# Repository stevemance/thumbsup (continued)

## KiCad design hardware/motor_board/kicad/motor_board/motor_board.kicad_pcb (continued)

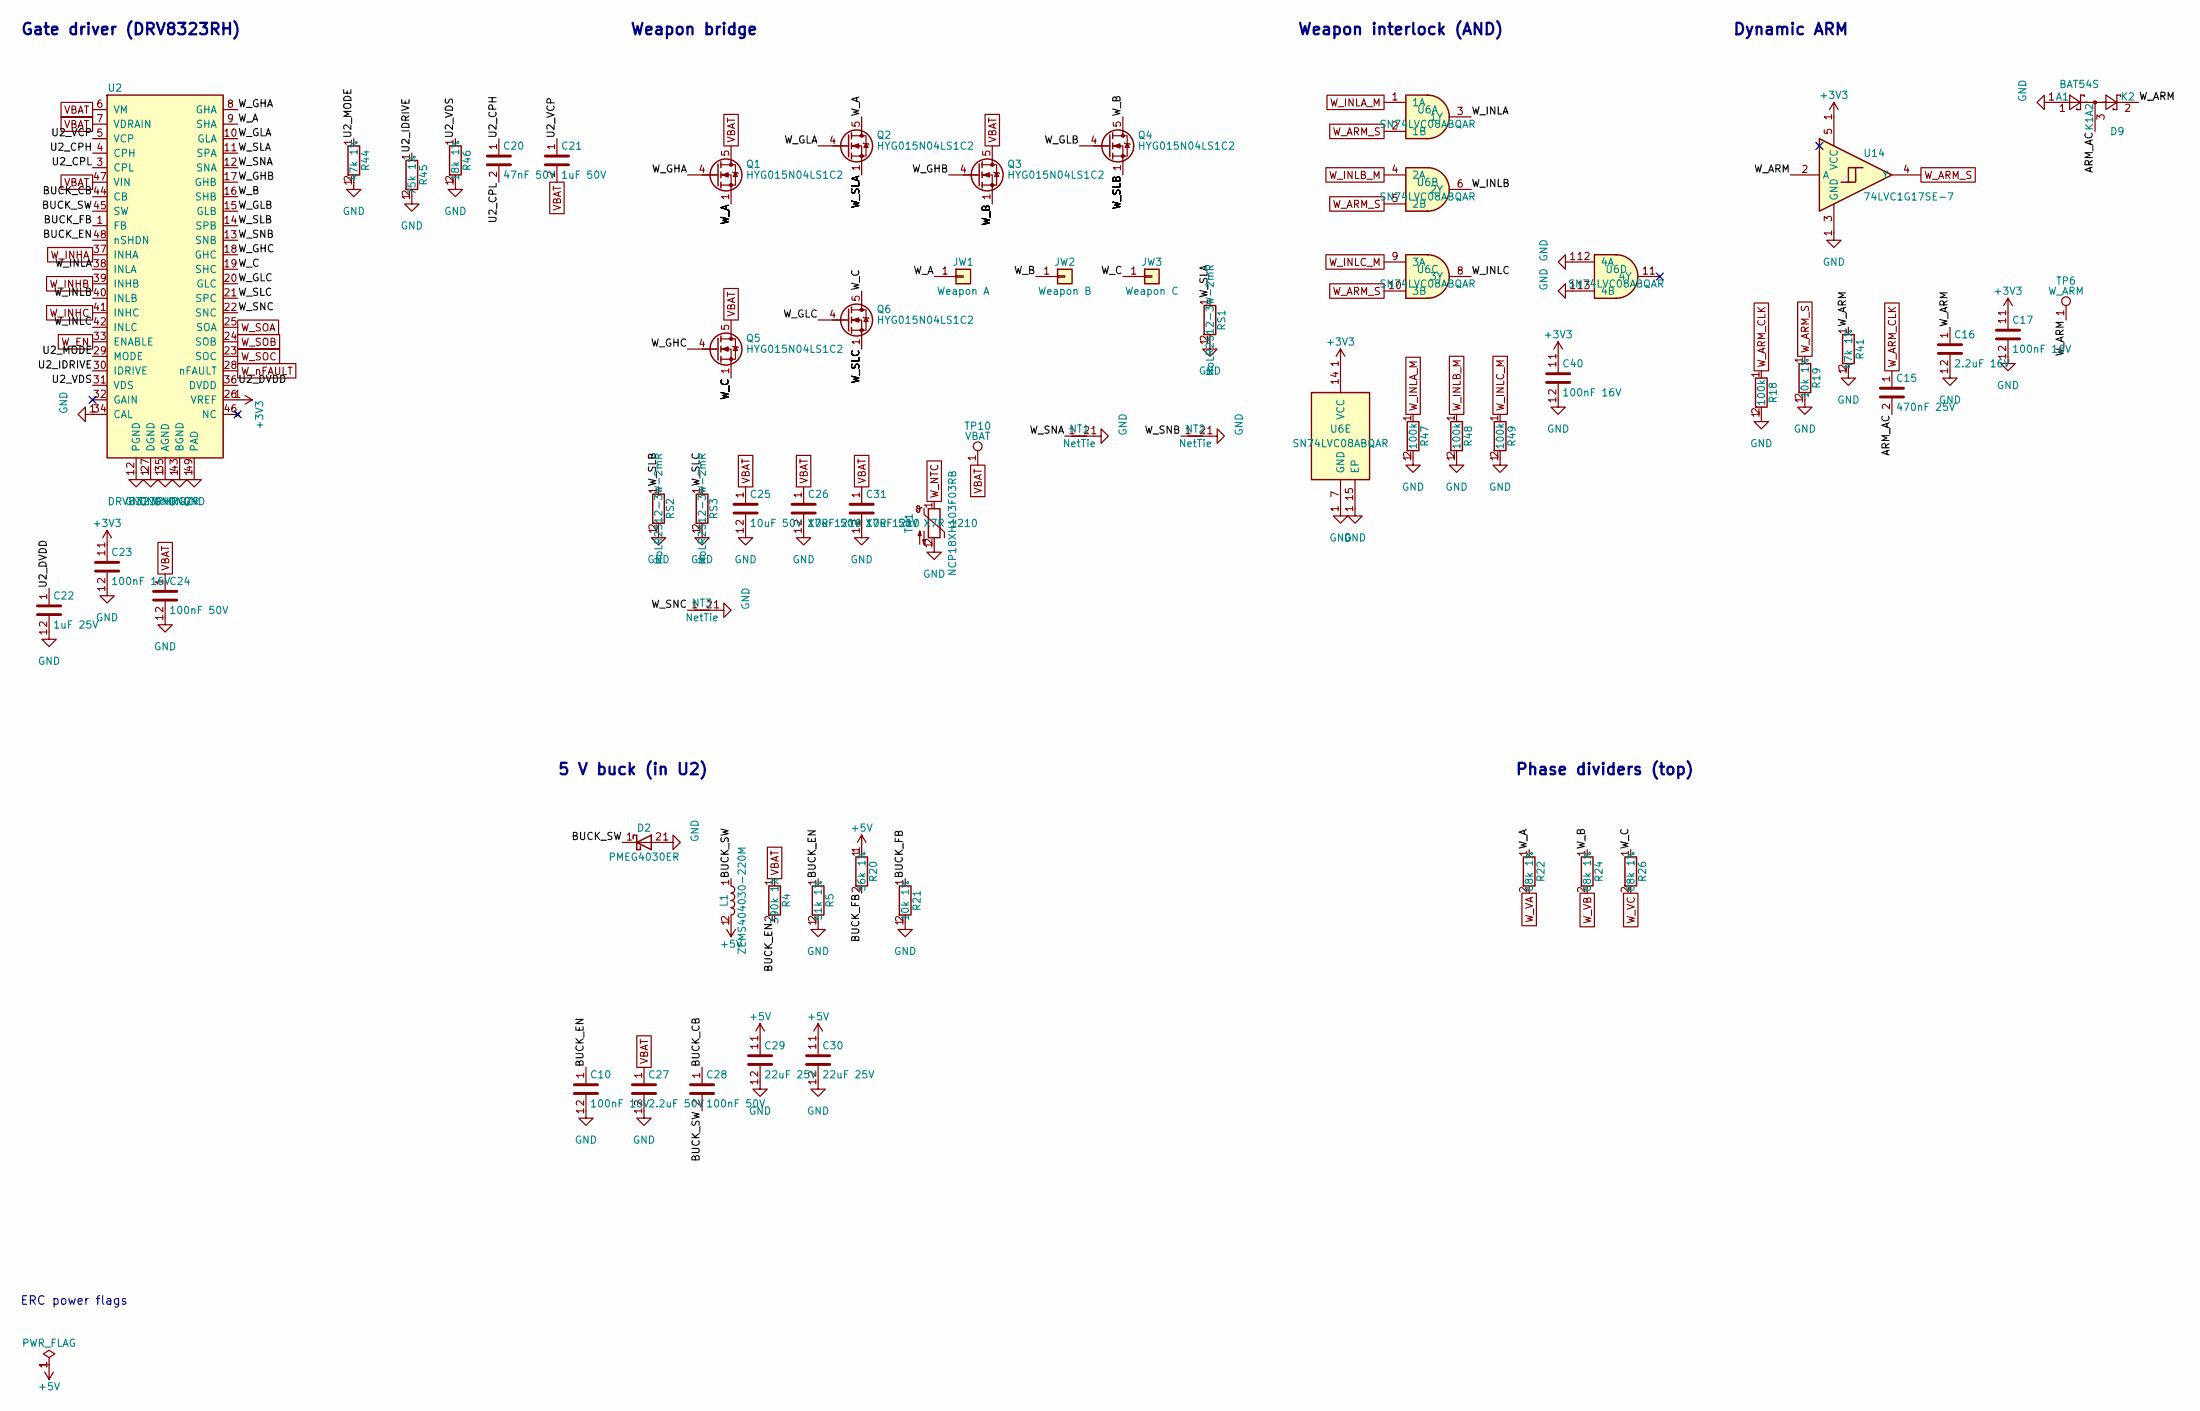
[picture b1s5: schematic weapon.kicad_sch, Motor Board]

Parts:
C10, C17, C23, C40: 100nF 16V; C_0402_1005Metric; LCSC C1525
C15: 470nF 25V; C_0603_1608Metric; LCSC C1623
C16: 2.2uF 16V; C_0603_1608Metric; LCSC C23630
C20: 47nF 50V; C_0603_1608Metric; LCSC C1622
C21: 1uF 50V; C_0603_1608Metric; LCSC C15849
C22: 1uF 25V; C_0402_1005Metric; LCSC C52923
C24, C28: 100nF 50V; C_0603_1608Metric; LCSC C14663
C25, C26, C31: 10uF 50V X7R 1210; C_1210_3225Metric; LCSC C77102
C27: 2.2uF 50V; C_0805_2012Metric; LCSC C377773
C29, C30: 22uF 25V; C_0805_2012Metric; LCSC C45783
D2: PMEG4030ER; Nexperia_CFP3_SOD-123W; MPN PMEG4030ER; LCSC C389355
D9: BAT54S; SOT-23; MPN BAT54S; LCSC C47546
JW1: Weapon A; SolderWire-1.5sqmm_1x01_D1.7mm_OD3.9mm
JW2: Weapon B; SolderWire-1.5sqmm_1x01_D1.7mm_OD3.9mm
JW3: Weapon C; SolderWire-1.5sqmm_1x01_D1.7mm_OD3.9mm
L1: ZEMS404030-220M; L_Changjiang_FTC404030S; MPN ZEMS404030-220M; LCSC C49009291
NT1, NT2, NT3: NetTie; NetTie-2_SMD_Pad0.5mm
Q1, Q2, Q3, Q4, Q5, Q6: HYG015N04LS1C2; PQFN-8-EP_6x5mm_P1.27mm_Generic; MPN HYG015N04LS1C2; LCSC C2874970
R4: 390k 1%; R_0603_1608Metric; LCSC C137735
R5: 51k 1%; R_0402_1005Metric; LCSC C25794
R18, R47, R48, R49: 100k; R_0402_1005Metric; LCSC C25741
R19, R21: 10k 1%; R_0402_1005Metric; LCSC C25744
R20: 56k 1%; R_0402_1005Metric; LCSC C25796
R22, R24, R26: 68k 1%; R_0402_1005Metric; LCSC C36871
R41, R44: 47k 1%; R_0402_1005Metric; LCSC C25792
R45: 75k 1%; R_0402_1005Metric; LCSC C25798
R46: 18k 1%; R_0402_1005Metric; LCSC C25762
RS1, RS2, RS3: HoLR2512-3W-2mR; R_2512_HoLR_1-4mR; MPN HoLR2512-3W-2mR; LCSC C2844506
TH1: NCP18XH103F03RB; R_0603_1608Metric; LCSC C13564
TP6: W_ARM; TestPoint_Pad_D1.0mm
TP10: VBAT; TestPoint_Pad_D1.0mm
U2: DRV8323RHRGZR; Texas_RGZ0048A_VQFN-48-1EP_7x7mm_P0.5mm_EP5.15x5.15mm; MPN DRV8323RHRGZR; LCSC C543035
U6: SN74LVC08ABQAR; DHWQFN-14-1EP_2.5x3mm_P0.5mm_EP1x1.5mm; MPN SN74LVC08ABQAR; LCSC C31971766
U14: 74LVC1G17SE-7; SOT-353_SC-70-5; MPN 74LVC1G17SE-7; LCSC C212314

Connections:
+3V3: C17.1, C23.1, C40.1, U2.26 (VREF), U6.14 (VCC), U14.5 (VCC); also elsewhere on the board
+5V: C29.1, C30.1, L1.2, R20.1; also elsewhere on the board
/weapon/ARM_AC: C15.2, D9.3 (K1A2)
/weapon/BUCK_CB: C28.1, U2.44 (CB)
/weapon/BUCK_EN: C10.1, R4.2, R5.1, U2.48 (nSHDN)
/weapon/BUCK_FB: R20.2, R21.1, U2.1 (FB)
/weapon/BUCK_SW: C28.2, D2.1 (K), L1.1, U2.45 (SW)
/weapon/U2_CPH: C20.1, U2.4 (CPH)
/weapon/U2_CPL: C20.2, U2.3 (CPL)
/weapon/U2_DVDD: C22.1, U2.36 (DVDD)
/weapon/U2_IDRIVE: R45.1, U2.30 (IDRIVE)
/weapon/U2_MODE: R44.1, U2.29 (MODE)
/weapon/U2_VCP: C21.1, U2.5 (VCP)
/weapon/U2_VDS: R46.1, U2.31 (VDS)
/weapon/W_A: JW1.1, Q1.1 (S), Q1.2 (S), Q1.3 (S), Q2.5 (D), R22.1, U2.9 (SHA)
/weapon/W_ARM: C16.1, D9.2 (K2), R41.1, TP6.1, U14.2 (A)
/weapon/W_B: JW2.1, Q3.1 (S), Q3.2 (S), Q3.3 (S), Q4.5 (D), R24.1, U2.16 (SHB)
/weapon/W_C: JW3.1, Q5.1 (S), Q5.2 (S), Q5.3 (S), Q6.5 (D), R26.1, U2.19 (SHC)
/weapon/W_GHA: Q1.4 (G), U2.8 (GHA)
/weapon/W_GHB: Q3.4 (G), U2.17 (GHB)
/weapon/W_GHC: Q5.4 (G), U2.18 (GHC)
/weapon/W_GLA: Q2.4 (G), U2.10 (GLA)
/weapon/W_GLB: Q4.4 (G), U2.15 (GLB)
/weapon/W_GLC: Q6.4 (G), U2.20 (GLC)
/weapon/W_INLA: U2.38 (INLA), U6.3 (1Y)
/weapon/W_INLB: U2.40 (INLB), U6.6 (2Y)
/weapon/W_INLC: U2.42 (INLC), U6.8 (3Y)
/weapon/W_SLA: Q2.1 (S), Q2.2 (S), Q2.3 (S), RS1.1, U2.11 (SPA)
/weapon/W_SLB: Q4.1 (S), Q4.2 (S), Q4.3 (S), RS2.1, U2.14 (SPB)
/weapon/W_SLC: Q6.1 (S), Q6.2 (S), Q6.3 (S), RS3.1, U2.21 (SPC)
/weapon/W_SNA: NT1.1, U2.12 (SNA)
/weapon/W_SNB: NT2.1, U2.13 (SNB)
/weapon/W_SNC: NT3.1, U2.22 (SNC)
GND: C10.2, C16.2, C17.2, C22.2, C23.2, C24.2, C25.2, C26.2, C27.2, C29.2, C30.2, C31.2, C40.2, D2.2 (A), D9.1 (A1), NT1.2, NT2.2, NT3.2, R5.2, R18.2, R19.2, R21.2, R41.2, R44.2, R45.2, R46.2, R47.2, R48.2, R49.2, RS1.2, RS2.2, RS3.2, TH1.2, U2.2 (PGND), U2.27 (DGND), U2.34 (CAL), U2.35 (AGND), U2.43 (BGND), U2.49 (PAD), U6.7 (GND), U6.12 (4A), U6.13 (4B), U6.15 (EP), U14.3 (GND); also elsewhere on the board
VBAT: C21.2, C24.1, C25.1, C26.1, C27.1, C31.1, Q1.5 (D), Q3.5 (D), Q5.5 (D), R4.1, TP10.1, U2.6 (VM), U2.7 (VDRAIN), U2.47 (VIN); also elsewhere on the board
W_ARM_CLK: C15.1, R18.1; also elsewhere on the board
W_ARM_S: R19.1, U6.2 (1B), U6.5 (2B), U6.10 (3B), U14.4 (Y); also elsewhere on the board
W_EN: U2.33 (ENABLE); also elsewhere on the board
W_INHA: U2.37 (INHA); also elsewhere on the board
W_INHB: U2.39 (INHB); also elsewhere on the board
W_INHC: U2.41 (INHC); also elsewhere on the board
W_INLA_M: R47.1, U6.1 (1A); also elsewhere on the board
W_INLB_M: R48.1, U6.4 (2A); also elsewhere on the board
W_INLC_M: R49.1, U6.9 (3A); also elsewhere on the board
W_NTC: TH1.1; also elsewhere on the board
W_SOA: U2.25 (SOA); also elsewhere on the board
W_SOB: U2.24 (SOB); also elsewhere on the board
W_SOC: U2.23 (SOC); also elsewhere on the board
W_VA: R22.2; also elsewhere on the board
W_VB: R24.2; also elsewhere on the board
W_VC: R26.2; also elsewhere on the board
W_nFAULT: U2.28 (nFAULT); also elsewhere on the board

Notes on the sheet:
ERC power flags
Gate driver (DRV8323RH)
Weapon bridge
Weapon interlock (AND)
Dynamic ARM
5 V buck (in U2)
Phase dividers (top)

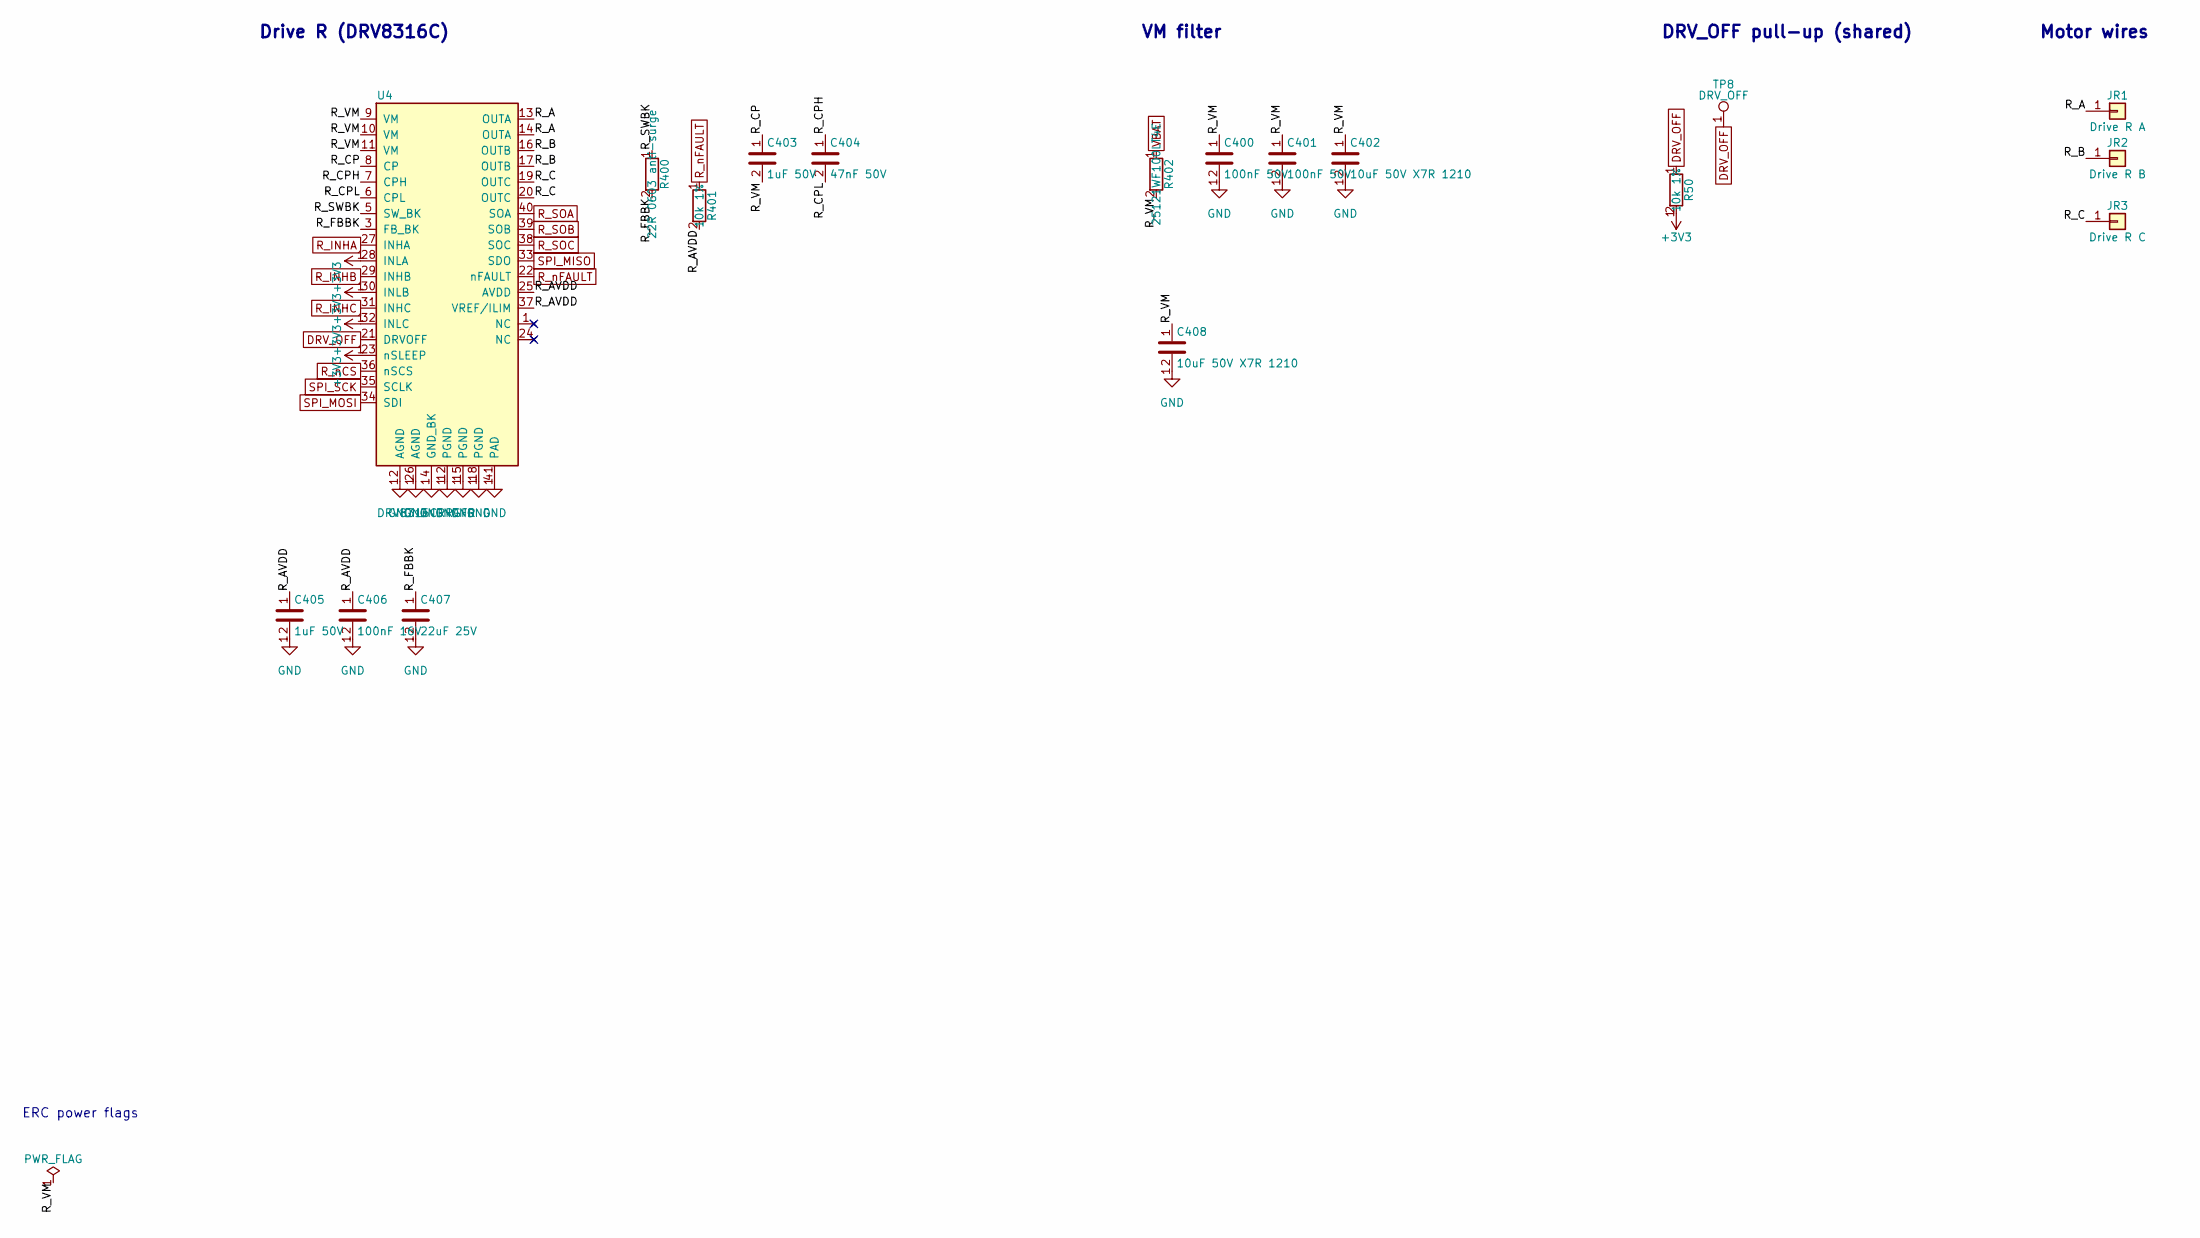
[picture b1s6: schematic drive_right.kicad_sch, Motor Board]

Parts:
C400, C401: 100nF 50V; C_0603_1608Metric; LCSC C14663
C402, C408: 10uF 50V X7R 1210; C_1210_3225Metric; LCSC C77102
C403, C405: 1uF 50V; C_0603_1608Metric; LCSC C15849
C404: 47nF 50V; C_0603_1608Metric; LCSC C1622
C406: 100nF 16V; C_0402_1005Metric; LCSC C1525
C407: 22uF 25V; C_0805_2012Metric; LCSC C45783
JR1: Drive R A; SolderWire-0.5sqmm_1x01_D0.9mm_OD2.1mm
JR2: Drive R B; SolderWire-0.5sqmm_1x01_D0.9mm_OD2.1mm
JR3: Drive R C; SolderWire-0.5sqmm_1x01_D0.9mm_OD2.1mm
R50, R401: 10k 1%; R_0402_1005Metric; LCSC C25744
R400: 22R 0603 anti-surge; R_0603_1608Metric; LCSC C2074038
R402: 25121WF100LT4E; R_2512_6332Metric; MPN 25121WF100LT4E; LCSC C25466
TP8: DRV_OFF; TestPoint_Pad_D1.0mm
U4: DRV8316CRRGFR; TI_RGF0040E_VQFN-40-1EP_5x7mm_P0.5mm_EP3.7x5.7mm; MPN DRV8316CRRGFR; LCSC C5447274

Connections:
+3V3: R50.2, U4.23 (nSLEEP), U4.28 (INLA), U4.30 (INLB), U4.32 (INLC); also elsewhere on the board
/drive_right/R_A: JR1.1, U4.13 (OUTA), U4.14 (OUTA)
/drive_right/R_AVDD: C405.1, C406.1, R401.2, U4.25 (AVDD), U4.37 (VREF/ILIM)
/drive_right/R_B: JR2.1, U4.16 (OUTB), U4.17 (OUTB)
/drive_right/R_C: JR3.1, U4.19 (OUTC), U4.20 (OUTC)
/drive_right/R_CP: C403.1, U4.8 (CP)
/drive_right/R_CPH: C404.1, U4.7 (CPH)
/drive_right/R_CPL: C404.2, U4.6 (CPL)
/drive_right/R_FBBK: C407.1, R400.2, U4.3 (FB_BK)
/drive_right/R_SWBK: R400.1, U4.5 (SW_BK)
/drive_right/R_VM: C400.1, C401.1, C402.1, C403.2, C408.1, R402.2, U4.9 (VM), U4.10 (VM), U4.11 (VM)
DRV_OFF: R50.1, TP8.1, U4.21 (DRVOFF); also elsewhere on the board
GND: C400.2, C401.2, C402.2, C405.2, C406.2, C407.2, C408.2, U4.2 (AGND), U4.4 (GND_BK), U4.12 (PGND), U4.15 (PGND), U4.18 (PGND), U4.26 (AGND), U4.41 (PAD); also elsewhere on the board
R_INHA: U4.27 (INHA); also elsewhere on the board
R_INHB: U4.29 (INHB); also elsewhere on the board
R_INHC: U4.31 (INHC); also elsewhere on the board
R_SOA: U4.40 (SOA); also elsewhere on the board
R_SOB: U4.39 (SOB); also elsewhere on the board
R_SOC: U4.38 (SOC); also elsewhere on the board
R_nCS: U4.36 (nSCS); also elsewhere on the board
R_nFAULT: R401.1, U4.22 (nFAULT); also elsewhere on the board
SPI_MISO: U4.33 (SDO); also elsewhere on the board
SPI_MOSI: U4.34 (SDI); also elsewhere on the board
SPI_SCK: U4.35 (SCLK); also elsewhere on the board
VBAT: R402.1; also elsewhere on the board

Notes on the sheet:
ERC power flags
Drive R (DRV8316C)
VM filter
DRV_OFF pull-up (shared)
Motor wires

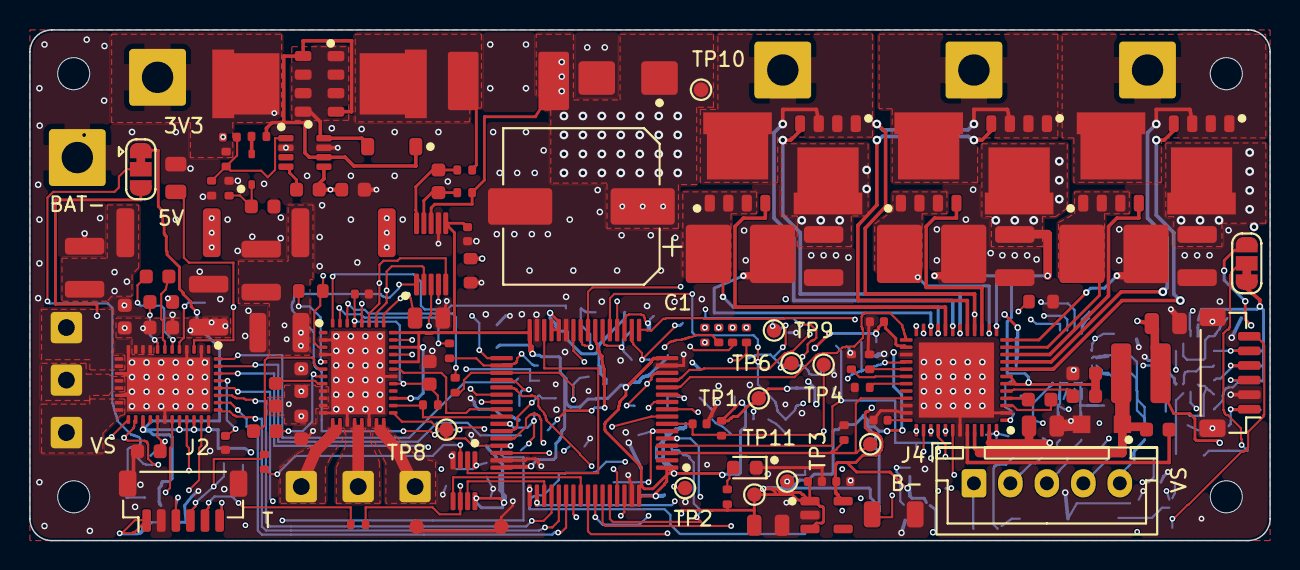
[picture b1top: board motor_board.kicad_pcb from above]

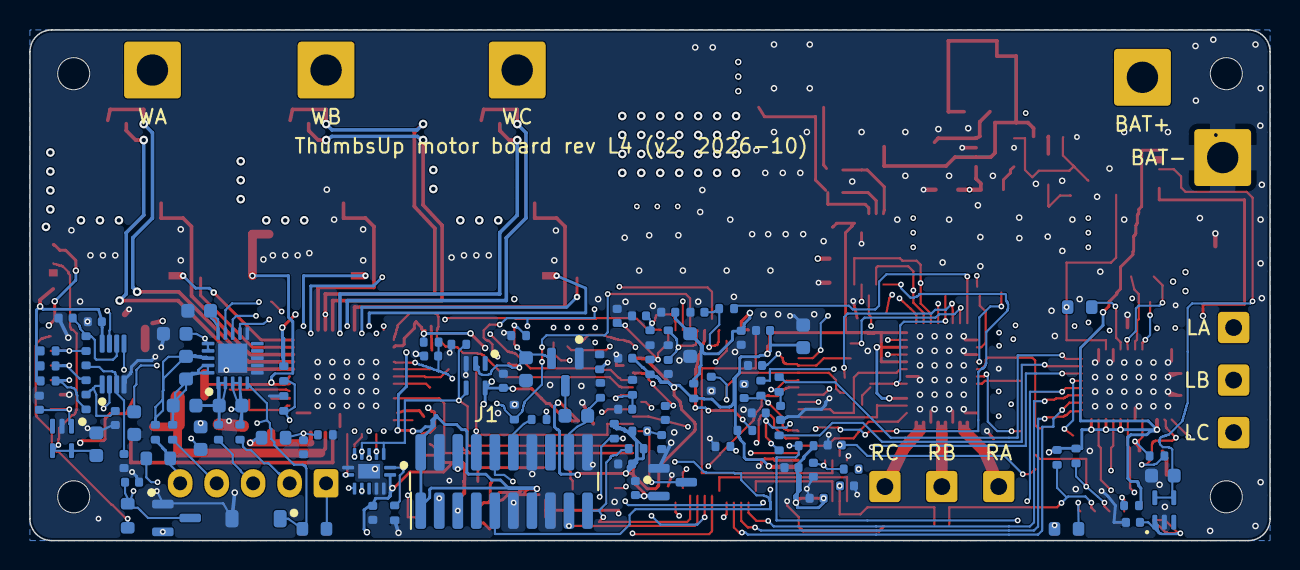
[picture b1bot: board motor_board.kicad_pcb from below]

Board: 4 copper layers, 85.0 x 35.0 mm, 233 parts (105 on the bottom side), 159 nets.

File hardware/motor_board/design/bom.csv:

Comment,Designator,Footprint,LCSC Part #,Qty
330uF 35V hybrid polymer,C1,CP_Elec_10x10.5,C278516,1
4.7uF 16V,"C11,C45,C48,C64,C66",C_0603_1608Metric,C19666,5
220nF 25V,"C12,C4,C5,C6,C7,C8",C_0603_1608Metric,C21120,6
22nF 50V,C13,C_0603_1608Metric,C21122,1
100nF 100V,C14,C_0603_1608Metric,C15725,1
470nF 25V,C15,C_0603_1608Metric,C1623,1
2.2uF 16V,C16,C_0603_1608Metric,C23630,1
100nF 16V,"C10,C17,C18,C23,C3,C306,C40,C406,C44,C47,C50,C60,C61,C62,C63,C65,C67,C68,C71,C72,C73,C74",C_0402_1005Metric,C1525,22
100nF 50V,"C117,C2,C24,C28,C300,C301,C400,C401",C_0603_1608Metric,C14663,8
47nF 50V,"C20,C304,C404",C_0603_1608Metric,C1622,3
1uF 50V,"C21,C303,C305,C403,C405",C_0603_1608Metric,C15849,5
1uF 25V,"C22,C46,C49,C69,C70",C_0402_1005Metric,C52923,5
10uF 50V X7R 1210,"C25,C26,C302,C308,C31,C402,C408",C_1210_3225Metric,C77102,7
2.2uF 50V,C27,C_0805_2012Metric,C377773,1
22uF 25V,"C29,C30,C307,C407",C_0805_2012Metric,C45783,4
1nF 50V,"C19,C41,C42,C43",C_0402_1005Metric,C1523,4
22pF C0G,"C80,C81,C82,C90,C91,C92",C_0402_1005Metric,C1555,6
4.7uF 50V X7R,C9,C_1206_3216Metric,C29823,1
SMBJ20A,D1,D_SMB,C151922,1
1N4148WS,D10,D_SOD-323,C2128,1
PMEG4030ER 40V 3A,D2,Nexperia_CFP3_SOD-123W,C389355,1
LED red,D3,LED_0603_1608Metric,C2286,1
MMSZ5242B 12V,D4,D_SOD-123,C21567,1
B5819W,D5,D_SOD-123,C8598,1
BAV99,"D7,D8",SOT-23,C2500,2
BAT54S,D9,SOT-23,C47546,1
B2B 2x10 1.27mm male,J1,BOOMELE_1.27-2x10P_SMD,C59981,1
SH1.0 6P SMD vertical,"J2,J3",JST_SH_BM06B-SRSS-TB_1x06-1MP_P1.00mm_Vertical,C160392,2
JST XH 5-pin vertical (balance),J4,JST_XH_B5B-XH-A_1x05_P2.50mm_Vertical,C157991,1
ZEMS404030-220M 22uH,L1,L_Changjiang_FTC404030S,C49009291,1
HYG015N04LS1C2,"Q1,Q2,Q3,Q4,Q5,Q6,Q7,Q8",PQFN-8-EP_6x5mm_P1.27mm_Generic,C2874970,8
4.7k,"R1,R54,R55,R56,R57,R58,R59",R_0402_1005Metric,C25900,7
2.2k 0603,"R113,R117",R_0603_1608Metric,C4190,2
100k,"R12,R13,R18,R33,R40,R47,R48,R49",R_0402_1005Metric,C25741,8
15k 1%,R14,R_0402_1005Metric,C25756,1
6.8k 0603,R15,R_0603_1608Metric,C23212,1
10R,"R2,R3",R_0402_1005Metric,C25077,2
56k 1%,R20,R_0402_1005Metric,C25796,1
10k 1%,"R16,R17,R19,R21,R23,R25,R27,R301,R401,R42,R43,R50,R52,R53,R64",R_0402_1005Metric,C25744,15
68k 1%,"R22,R24,R26,R63",R_0402_1005Metric,C36871,4
22R 0603 anti-surge,"R300,R400",R_0603_1608Metric,C2074038,2
0.1R 1W 2512,"R302,R402",R_2512_6332Metric,C25466,2
1M,R32,R_0402_1005Metric,C26083,1
390k 1%,R4,R_0603_1608Metric,C137735,1
47k 1%,"R41,R44",R_0402_1005Metric,C25792,2
75k 1%,R45,R_0402_1005Metric,C25798,1
18k 1%,R46,R_0402_1005Metric,C25762,1
51k 1%,R5,R_0402_1005Metric,C25794,1
100R 0603,"R11,R6",R_0603_1608Metric,C22775,2
0R,R60,R_0402_1005Metric,C17168,1
1k,"R110,R111,R112,R114,R115,R116,R62",R_0402_1005Metric,C11702,7
100R,"R10,R7,R8,R9",R_0402_1005Metric,C25076,4
330R,"R70,R71,R72,R80,R81,R82",R_0402_1005Metric,C25104,6
2mR 1% 2512,"RS1,RS2,RS3",R_2512_HoLR_1-4mR,C2844506,3
1mR 1% 2512,RS4,R_2512_JIERR_RE_small_electrode,C46961745,1
NCP18XH103F03RB,TH1,R_0603_1608Metric,C13564,1
STM32G474RET6,U1,LQFP-64_10x10mm_P0.5mm,C521608,1
TPS22945DCKR,"U11,U12",SOT-353_SC-70-5,C47507,2
LM74502DDFR,U13,Texas_DDF0008A_SOT-8_1.6x2.9mm_P0.65mm,C3236215,1
74LVC1G17SE-7,U14,SOT-353_SC-70-5,C212314,1
DRV8323RHRGZR,U2,Texas_RGZ0048A_VQFN-48-1EP_7x7mm_P0.5mm_EP5.15x5.15mm,C543035,1
DRV8316CRRGFR,"U3,U4",TI_RGF0040E_VQFN-40-1EP_5x7mm_P0.5mm_EP3.7x5.7mm,C5447274,2
AP2112K-3.3TRG1,U5,SOT-23-5,C51118,1
SN74LVC08ABQAR,U6,DHWQFN-14-1EP_2.5x3mm_P0.5mm_EP1x1.5mm,C31971766,1
INA239AQDGSRQ1,U7,MSOP-10_3x3mm_P0.5mm,C4367136,1
BQ76907RGRR,U8,QFN-20-1EP_3.5x3.5mm_P0.5mm_EP2x2mm,C22458649,1
SN74LVC3G17DCUR,"U10,U9",VSSOP-8_2.3x2mm_P0.5mm,C68245,2

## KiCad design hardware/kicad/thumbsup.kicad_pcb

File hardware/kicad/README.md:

# ThumbsUp v1 KiCad project

Open `thumbsup.kicad_sch` in KiCad 10.  **Every `.kicad_sch` here is generated — edit
`../tools/sch/circuit.py` (connectivity) or `../tools/sch/layouts.py` (placement) and
rebuild.**

```bash
python3 -m venv hardware/tools/.venv
hardware/tools/.venv/bin/pip install -r hardware/tools/requirements.txt
hardware/tools/.venv/bin/python hardware/tools/sch/build.py --render
```

The build:

1. writes `thumbsup.kicad_sym` (AT32F421K8U7, FD6288Q with EP, HYG015N04LS1C2 with the PDFN pin
   numbering, SK6812MINI-C, a Pico W symbol whose ground pins are typed correctly) and
   `thumbsup.pretty` (SK6812MINI-C land pattern, Kelvin 2512 shunt, 30 A motor pads),
2. builds the SKiDL circuit, runs SKiDL ERC and writes `thumbsup.net`,
3. draws every sheet with explicit placement,
4. runs `kicad-cli sch erc` (summary printed, full report in `erc.json`),
5. exports `thumbsup_kicad.net` and checks that its (ref, pin) partition is identical to
   SKiDL's — the build fails if the drawing does not match the circuit,
6. with `--render`, writes one PNG per sheet into `preview/`.

| Sheet | File | Contents |
|---|---|---|
| Root | `thumbsup.kicad_sch` | sheet index |
| Pack | `thumbsup_pack.kicad_sch` | XT30, TVS, 1 mΩ shunt, reverse-polarity P-FET |
| Rails | `thumbsup_rails.kicad_sch` | AP63205 5 V, D3 to VSYS, 2× AP2112, monitors, power LED |
| Pico | `thumbsup_pico.kicad_sch` | Pico W, I2C pull-ups, ARM link, reset, NTC, expansion |
| Sense | `thumbsup_sense.kicad_sch` | INA226 ×4 with filters, LSM6DS3TR-C, ADXL375 |
| IO | `thumbsup_io.kicad_sch` | W25Q128, 74AHCT1G125, SK6812 ×2 |
| ESC L/R/W | `thumbsup_esc_{l,r,w}.kicad_sch` | AT32 + FD6288Q + sense networks (+ weapon enable on W) |
| Bridges | `thumbsup_esc_{l,r,w}_bridge.kicad_sch` | 3 half-bridges, bootstrap, shunt, bulk, motor pads |

Conventions: rails are power symbols, cross-sheet signals are global labels
(`L_HO1`, `MOTOR_W_A`, `I_L+`, `I_L_S+` …), sheet-local nets are plain labels.  Decoupling
capacitors are drawn in a strip per sheet with the IC they belong to in the title.  Kelvin
sense nets (`*_S+/-`) join the power nets only through `NT*` net-ties that must sit on the
shunt pads.  Parts with `(dnp yes)` (R201/R301/R401) are footprints only.  Every part carries
a hidden `Note` property with its placement intent.

`thumbsup.kicad_pcb` is an empty board — layout has not started.

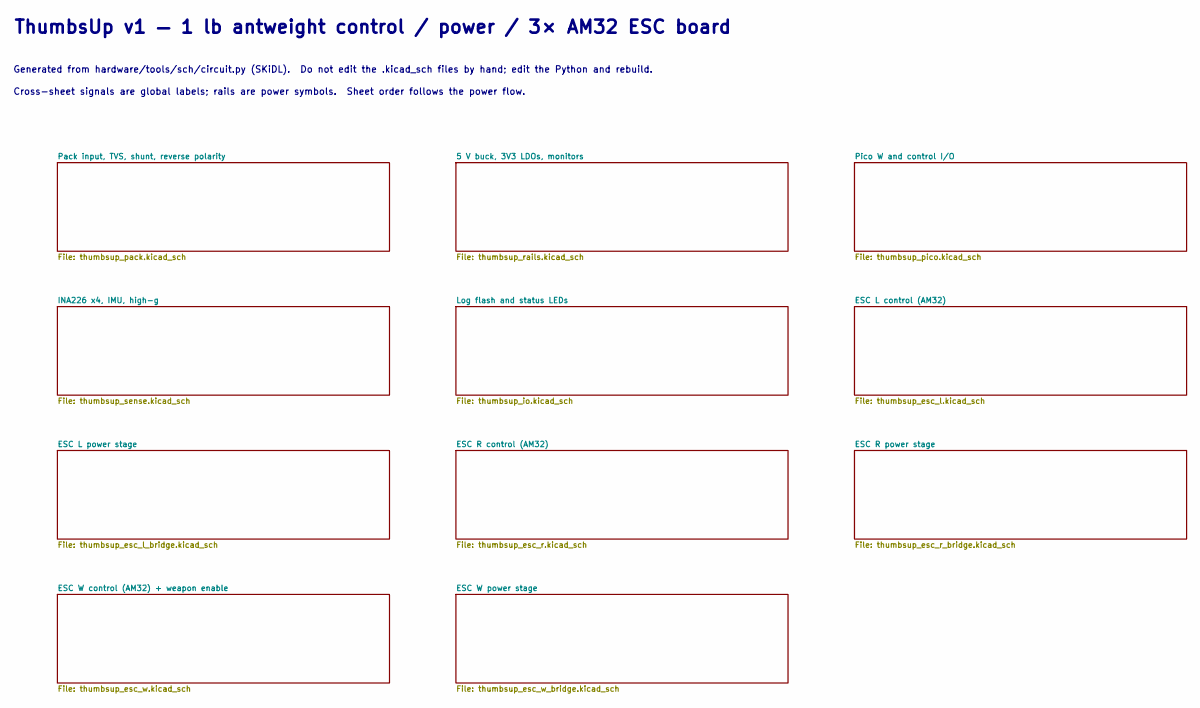
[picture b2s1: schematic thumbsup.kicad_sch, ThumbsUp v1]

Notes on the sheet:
ThumbsUp v1 — 1 lb antweight control / power / 3× AM32 ESC board
Generated from hardware/tools/sch/circuit.py (SKiDL). Do not edit the .kicad_sch files by hand; edit the Python and rebuild.
Cross-sheet signals are global labels; rails are power symbols. Sheet order follows the power flow.

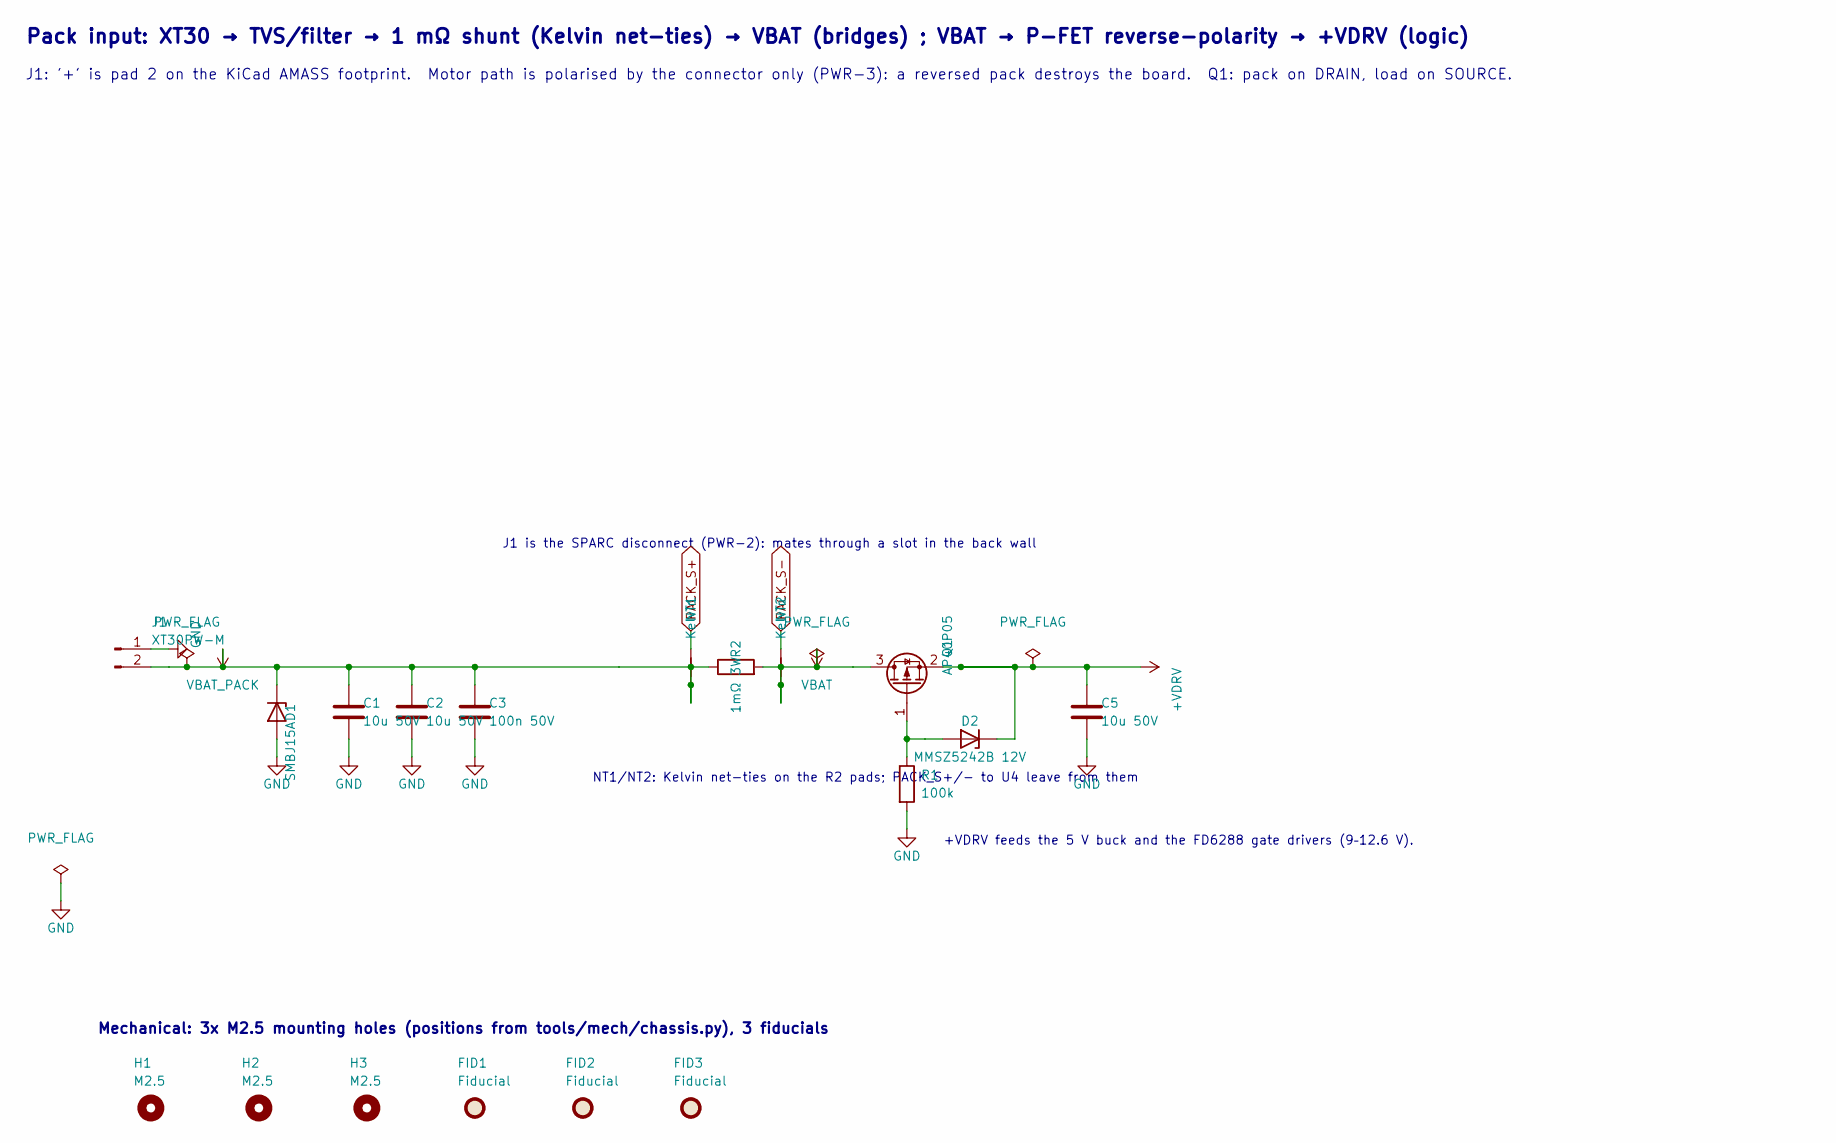
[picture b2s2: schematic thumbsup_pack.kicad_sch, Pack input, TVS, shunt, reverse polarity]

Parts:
C1, C2, C5: 10u 50V; C_1206_3216Metric; LCSC C13585
C3: 100n 50V; C_0603_1608Metric; LCSC C14663
D1: SMBJ15A; D_SMB; LCSC C699013
D2: MMSZ5242B 12V; D_SOD-123; LCSC C21567
FID1, FID2, FID3: Fiducial; Fiducial_1mm_Mask2mm; JLC no BOM
H1, H2, H3: M2.5; MountingHole_2.7mm_M2.5; JLC no BOM
J1: XT30PW-M; AMASS_XT30PW-M_1x02_P2.50mm_Horizontal; LCSC C431092
NT1, NT2: Kelvin; NetTie-2_Kelvin_0.4mm
Q1: AP40P05; SOT-23; LCSC C2886385
R1: 100k; R_0402_1005Metric; LCSC C25741
R2: 1mΩ 3W; R_2512_Shunt_Kelvin; LCSC C46961745

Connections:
+VDRV: C5.1, D2.1 (K), Q1.2 (S); also elsewhere on the board
GND: C1.2, C2.2, C3.2, C5.2, D1.2 (A), J1.1, R1.2; also elsewhere on the board
unnamed: D2.2 (A), Q1.1 (G), R1.1
PACK_S+: NT1.2; also elsewhere on the board
PACK_S-: NT2.2; also elsewhere on the board
VBAT: NT2.1, Q1.3 (D), R2.2; also elsewhere on the board
VBAT_PACK: C1.1, C2.1, C3.1, D1.1 (K), J1.2, NT1.1, R2.1

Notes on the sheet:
Pack input: XT30 → TVS/filter → 1 mΩ shunt (Kelvin net-ties) → VBAT (bridges) ; VBAT → P-FET reverse-polarity → +VDRV (logic)
J1: '+' is pad 2 on the KiCad AMASS footprint. Motor path is polarised by the connector only (PWR-3): a reversed pack destroys the board. Q1: pack on DRAIN, load on SOURCE.
J1 is the SPARC disconnect (PWR-2): mates through a slot in the back wall
NT1/NT2: Kelvin net-ties on the R2 pads; PACK_S+/- to U4 leave from them
+VDRV feeds the 5 V buck and the FD6288 gate drivers (9–12.6 V).
Mechanical: 3x M2.5 mounting holes (positions from tools/mech/chassis.py), 3 fiducials

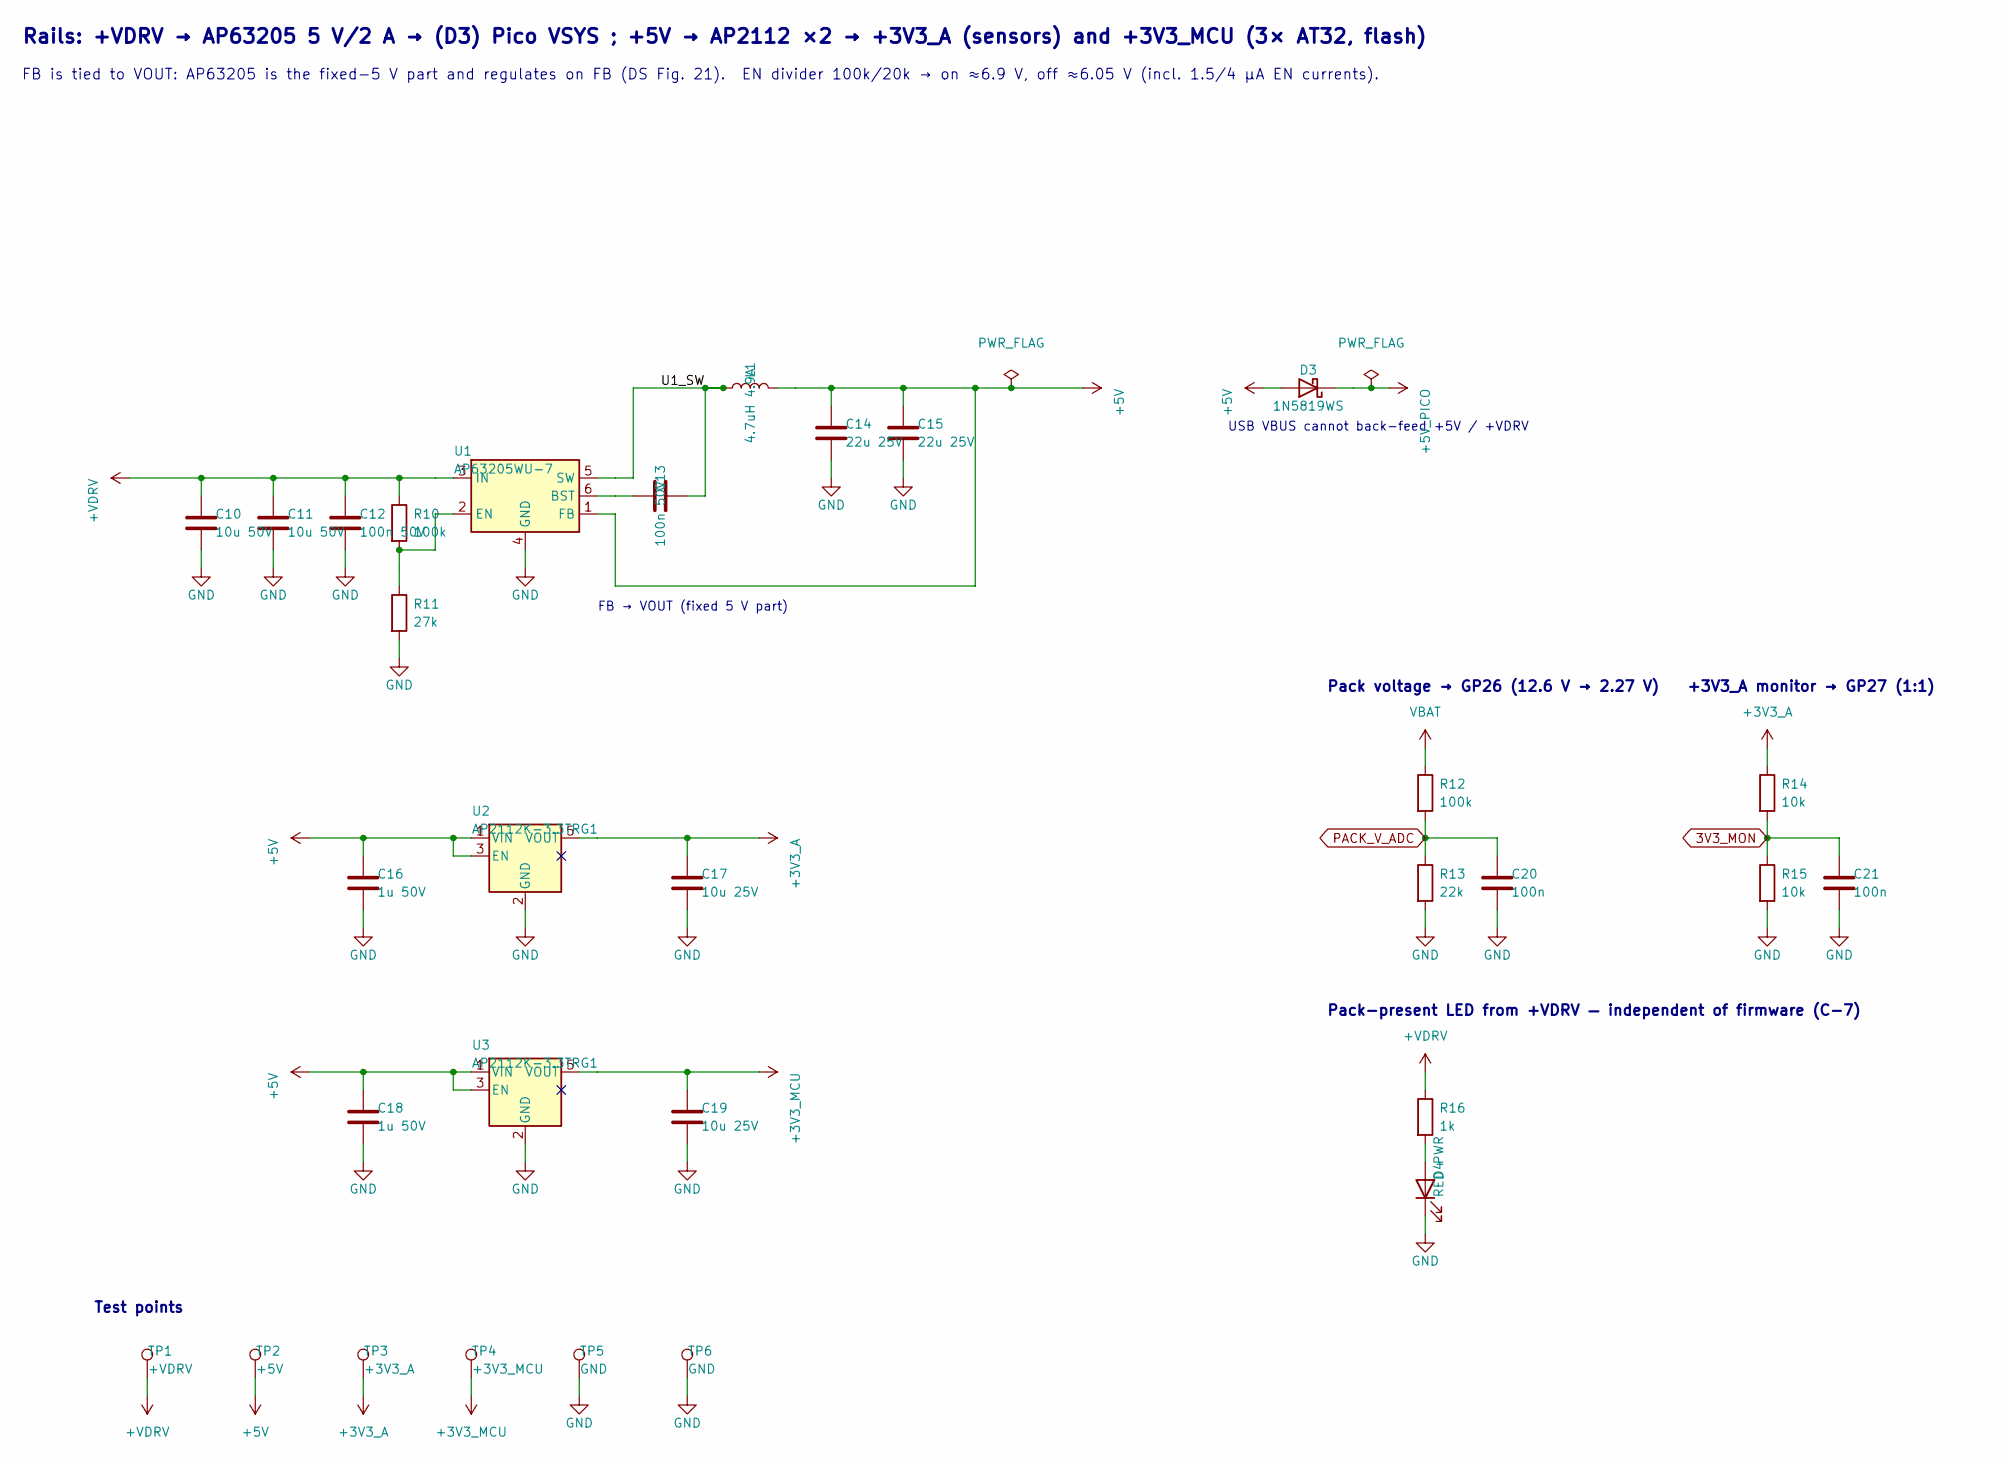
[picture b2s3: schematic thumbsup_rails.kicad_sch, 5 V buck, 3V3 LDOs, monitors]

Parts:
C10, C11: 10u 50V; C_1206_3216Metric; LCSC C13585
C12, C13: 100n 50V; C_0603_1608Metric; LCSC C14663
C14, C15: 22u 25V; C_0805_2012Metric; LCSC C45783
C16, C18: 1u 50V; C_0603_1608Metric; LCSC C15849
C17, C19: 10u 25V; C_0805_2012Metric; LCSC C15850
C20, C21: 100n; C_0402_1005Metric; LCSC C1525
D3: 1N5819WS; D_SOD-323; LCSC C191023
D4: RED PWR; LED_0603_1608Metric; LCSC C2286
L1: 4.7uH 4.9A; L_Changjiang_FNR4020S; LCSC C602031
R10, R12: 100k; R_0402_1005Metric; LCSC C25741
R11: 27k; R_0402_1005Metric; LCSC C25771
R13: 22k; R_0402_1005Metric; LCSC C25768
R14, R15: 10k; R_0402_1005Metric; LCSC C25744
R16: 1k; R_0402_1005Metric; LCSC C11702
TP1: +VDRV; TestPoint_Pad_D1.5mm
TP2: +5V; TestPoint_Pad_D1.5mm
TP3: +3V3_A; TestPoint_Pad_D1.5mm
TP4: +3V3_MCU; TestPoint_Pad_D1.5mm
TP5, TP6: GND; TestPoint_Pad_D1.5mm
U1: AP63205WU-7; TSOT-23-6; LCSC C2071056
U2, U3: AP2112K-3.3TRG1; SOT-23-5; LCSC C51118

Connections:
3V3_MON: C21.1, R14.2, R15.1; also elsewhere on the board
+3V3_A: C17.1, R14.1, TP3.1, U2.5 (VOUT); also elsewhere on the board
+3V3_MCU: C19.1, TP4.1, U3.5 (VOUT); also elsewhere on the board
+5V: C14.1, C15.1, C16.1, C18.1, D3.2 (A), L1.2, TP2.1, U1.1 (FB), U2.1 (VIN), U2.3 (EN), U3.1 (VIN), U3.3 (EN); also elsewhere on the board
+5V_PICO: D3.1 (K); also elsewhere on the board
+VDRV: C10.1, C11.1, C12.1, R10.1, R16.1, TP1.1, U1.3 (IN); also elsewhere on the board
/5 V buck, 3V3 LDOs, monitors/U1_SW: C13.2, L1.1, U1.5 (SW)
GND: C10.2, C11.2, C12.2, C14.2, C15.2, C16.2, C17.2, C18.2, C19.2, C20.2, C21.2, D4.1 (K), R11.2, R13.2, R15.2, TP5.1, TP6.1, U1.4 (GND), U2.2 (GND), U3.2 (GND); also elsewhere on the board
unnamed: D4.2 (A), R16.2
unnamed: C13.1, U1.6 (BST)
unnamed: R10.2, R11.1, U1.2 (EN)
PACK_V_ADC: C20.1, R12.2, R13.1; also elsewhere on the board
VBAT: R12.1; also elsewhere on the board

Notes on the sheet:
Rails: +VDRV → AP63205 5 V/2 A → (D3) Pico VSYS ; +5V → AP2112 ×2 → +3V3_A (sensors) and +3V3_MCU (3× AT32, flash)
FB is tied to VOUT: AP63205 is the fixed-5 V part and regulates on FB (DS Fig. 21). EN divider 100k/20k → on ≈6.9 V, off ≈6.05 V (incl. 1.5/4 µA EN currents).
FB → VOUT (fixed 5 V part)
USB VBUS cannot back-feed +5V / +VDRV
Pack voltage → GP26 (12.6 V → 2.27 V)
+3V3_A monitor → GP27 (1:1)
Test points
Pack-present LED from +VDRV — independent of firmware (C-7)
